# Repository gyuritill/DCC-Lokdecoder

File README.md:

# DCC-Lokdecoder
## Description
DCC multifunction decoder for H0 locomotives
## Features
- 1 motor H-bridge output
  - 3.6 A peak current
  - PWM frequency configurable (1-40 kHz)
  - overcurrent and temperature protected
- 10 function outputs
  - 115 mA per output
  - F0f, F0r, AUX1 and AUX2 are dimmable *todo*
  - mappable to F0-F12 function keys
- DCC asymmetry can be detected (for automatic brake control) *todo*
## Hardware
- 4-layer PCB esigned in KiCAD
- fairly standard components (available from Digi-Key, Farnell, Mouser, etc...)
- hand solderable (I did it too)
- 4 debug LEDs (red, yellow, green and blue)

|  |  |
| :---: | :---: |
| top side | bottom side |

## Firmware
- Arduino compatible programming (behaves like an UNO)
- DCC decoding by [NmraDcc](https://github.com/mrrwa/NmraDcc) library

## JMRI integration

|  |  |  |  |  |  |
| :---: | :---: | :---: | :---: | :---: | :---: |
| Basic  | Motor | Basic speed control | Speed table | Function map | Advanced |

## Install guide

1. Get the PCB (e.g. [JLCPCB](https://jlcpcb.com/)) and the components (e.g. [mouser](https://www.mouser.at/), [digikey](https://www.digikey.at/))
2. Solder the components. The SOIC with exposed pad is a bit tricky, it can be soldered from the other side with a big tip and a lot of flux.
3. Install the Arduino bootloader using the pads 5V, GND, SCK, MISO, MOSI, RST and an Arduino. [Arduino as ISP](https://www.arduino.cc/en/Tutorial/BuiltInExamples/ArduinoISP)
4. Uncomment the line `#define RESET_FACTORY_DEFAULTS` to fill the EEPROM with the default CV values
5. Upload the code using the pads 5V, GND, RX, TX, DTR and a USB TTL UART cable [like this](https://www.mouser.at/ProductDetail/FTDI/TTL-232R-5V-WE/?qs=OMDV80DKjRpCUAS6UR9QpQ%3D%3D)
6. Re-comment the line `#define RESET_FACTORY_DEFAULTS` to avoid resetting to factory defaults every time.
7. Upload the code again.
8. Add the decoder XML file to JMRI. In DecoderPro select "File-> Import Decoder File..." and browse to the decoder [XML](JMRI_decoder_file/Public_Domain_GTI_green.xml). It will take some time, then adds the decoder definition to the database.
9. Connect the T1 and T2 pads to the programming track of your DCC system.
10. Add new locomotive with the "New Loco" button and then "Read type from decoder". It should detect the correct type:

11. If everything is fine, you can install the decoder into your locomotive!
### Pinout
| Pad | Function |
| :-- | :-- |
| M1 | Motor 1 |
| M2 | Motor 2 |
| T1 | Track 1 |
| T2 | Track 2 |
| V+ | Positive common for function outputs (keep-alive capacitor positive) |
| F0f | F0 function output forward (open drain) |
| F0r | F0 function output reverse (open drain) |
| 1-8 | AUX function output n (open drain) |
| 5V | internal microcontroller +5V supply |
| GND | ground (keep alive capacitor negative) |
| SCK | ISP programming clock (connect to ISP SCK) |
| MISO | ISP programming read (connect to ISP MISO) |
| MOSI | ISP programming write (connect to ISP MOSI) |
| RST | ISP programming reset (connect to ISP reset output)
| RX | serial programming receive (connect to TTL UART TX) |
| TX | serial programming transmit (connect to TTL UART RX) |
| DTR | serial programming reset through a 100 nF capacitor (connect to TTL UART DTR) |

## Todo list
- [ ] CV15, CV16 decoder locking
- [ ] CV65 kick start
- [ ] CV67-94 speed table
- [ ] CV27 automatic brake control
- [ ] function output dimming
- [ ] motor fault check

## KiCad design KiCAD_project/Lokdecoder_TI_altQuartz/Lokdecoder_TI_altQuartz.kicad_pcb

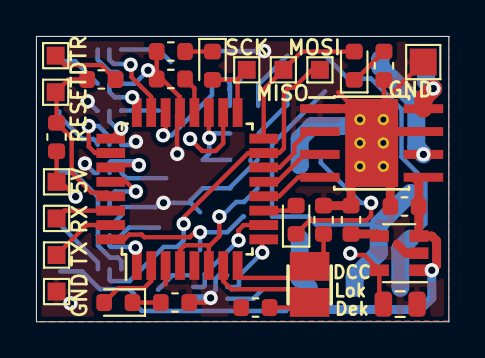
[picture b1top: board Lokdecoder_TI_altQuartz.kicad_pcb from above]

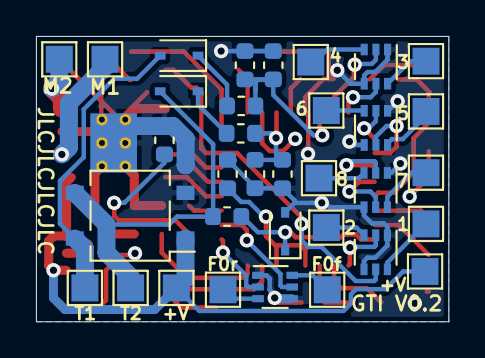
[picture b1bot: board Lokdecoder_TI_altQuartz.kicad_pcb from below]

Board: 4 copper layers, 22.9 x 15.8 mm, 63 parts (34 on the bottom side), 51 nets.

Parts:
C1, C2, C5, C10: 100nF; C_0603_1608Metric
C3: 470pF; C_0603_1608Metric
C4: 2.2uF; C_0805_2012Metric
C6, C7: 4.7uF; C_0603_1608Metric
C8, C9: 10pF; C_0603_1608Metric
D1: D_Bridge_+-AA; TO-269AA
D2: MM3Z4V7ST1G; D_SOD-323
D3, D4: NSR0530HT1G; D_SOD-323
D5: Ye_LED; LED_0603_1608Metric
D6: Gr_LED; LED_0603_1608Metric
D7: Rd_LED; LED_0603_1608Metric
D8: Bl_LED; LED_0603_1608Metric
IC1: MIC5205-5.0YM5-TR; SOT-23-5
IC2: ATMEGA328P-AUR; TQFP-32_7x7mm_P0.8mm
IC3: DRV8872DDAR; Texas_HTSOP-8-1EP_3.9x4.9mm_P1.27mm_EP2.95x4.9mm_Mask2.4x3.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
R1, R5, R6: 4.7k; R_0603_1608Metric
R2, R3, R4: 27k; R_0603_1608Metric
R7, R9, R10, R11: 1k; R_0603_1608Metric
T1, T2, T3, T4, T5: 2N7002DWCT; SOT-363_SC-70-6
TP1: M1; TestPoint_Pad_1.5x1.5mm
TP2: M2; TestPoint_Pad_1.5x1.5mm
TP3: T1; TestPoint_Pad_1.5x1.5mm
TP4: T2; TestPoint_Pad_1.5x1.5mm
TP5: GND; TestPoint_Pad_1.5x1.5mm
TP6, TP17: +V; TestPoint_Pad_1.5x1.5mm
TP7: F0f; TestPoint_Pad_1.5x1.5mm
TP8: F0r; TestPoint_Pad_1.5x1.5mm
TP9: 1; TestPoint_Pad_1.5x1.5mm
TP10: 2; TestPoint_Pad_1.5x1.5mm
TP11: 3; TestPoint_Pad_1.5x1.5mm
TP12: 4; TestPoint_Pad_1.5x1.5mm
TP13: 5; TestPoint_Pad_1.5x1.5mm
TP14: 6; TestPoint_Pad_1.5x1.5mm
TP15: 7; TestPoint_Pad_1.5x1.5mm
TP16: 8; TestPoint_Pad_1.5x1.5mm
TP18: RESET; TestPoint_Pad_1.0x1.0mm
TP19: SCK; TestPoint_Pad_1.0x1.0mm
TP20: MISO; TestPoint_Pad_1.0x1.0mm
TP21: MOSI; TestPoint_Pad_1.0x1.0mm
TP22: 5V; TestPoint_Pad_1.0x1.0mm
TP23: RX; TestPoint_Pad_1.0x1.0mm
TP24: TX; TestPoint_Pad_1.0x1.0mm
TP25: DTR; TestPoint_Pad_1.0x1.0mm
TP26: GND; TestPoint_Pad_1.0x1.0mm
X1: 16M; Crystal_SMD_2520-2Pin_2.5x2.0mm_HandSoldering

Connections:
+5V: C4.1, C5.2, IC1.5, IC2.4, IC2.6, IC2.18, R1.2, TP22.1
/A0: IC2.23, T4.2
/A1: IC2.24, T4.5
/A2: IC2.25, T5.2
/A3: IC2.26, T5.5
/A4: IC2.27, T3.2
/A5: IC2.28, T3.5
/A6: C6.2, IC2.19, R3.1, R5.1
/A7: C7.2, IC2.22, R4.1, R6.1
/AUX1: T2.6, TP9.1
/AUX1_TTL: IC2.1, T2.2
/AUX2: T2.3, TP10.1
/AUX2_TTL: IC2.15, T2.5, TP21.1
/AUX3: T4.6, TP11.1
/AUX4: T4.3, TP12.1
/AUX5: T5.6, TP13.1
/AUX6: T5.3, TP14.1
/AUX7: T3.6, TP15.1
/AUX8: T3.3, TP16.1
/D0: IC2.30, TP23.1
/D1: IC2.31, TP24.1
/D2: D2.1, IC2.32, R2.1
/D4: D8.2, IC2.2
/D5: IC2.9, T1.2
/D6: IC2.10, T1.5
/D7: D7.2, IC2.11
/D8: IC2.12, IC3.4
/D9: IC2.13, IC3.3
/D10: IC2.14, IC3.2
/D12: D6.2, IC2.16, TP20.1
/D13: D5.2, IC2.17, TP19.1
/DCC1: D1.4, D4.2, TP3.1
/DCC2: D1.3, D3.2, R2.2, TP4.1
/DTR: C1.2, TP25.1
/F0f: T1.6, TP7.1
/F0r: T1.3, TP8.1
/MOT1: IC3.6, TP1.1
/MOT2: IC3.8, TP2.1
/RESET: C1.1, IC2.29, R1.1, TP18.1
GND: C2.2, C3.1, C4.2, C5.1, C6.1, C7.1, C8.1, C9.1, C10.1, D1.2, D2.2, IC1.2, IC2.3, IC2.5, IC2.21, IC3.1, IC3.7, IC3.9, R5.2, R6.2, R7.1, R9.1, R10.1, R11.1, T1.1, T1.4, T2.1, T2.4, T3.1, T3.4, T4.1, T4.4, T5.1, T5.4, TP5.1, TP26.1
unnamed: C2.1, IC2.20
unnamed: C3.2, IC1.4
unnamed: C8.2, IC2.7, X1.1
unnamed: C9.2, IC2.8, X1.2
unnamed: D3.1, R3.2
unnamed: D4.1, R4.2
unnamed: D5.1, R9.2
unnamed: D6.1, R10.2
unnamed: D7.1, R11.2
unnamed: D8.1, R7.2
VCC: C10.2, D1.1, IC1.1, IC1.3, IC3.5, TP6.1, TP17.1

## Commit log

2021-02-12 Initial commit
    Initial commit
2021-02-14 Trim added,
    Arduino code:
    Comments extended, code cleanup
    - CV15/CV16 locking: local variables (unlockNumber, lockingNumber) created
    - CV27 autstop: : local variable (autoStop) created
    - CV65 kick-off: local variable (kickStart) created
    - CV66/CV95 speed trimming: feature implemented
2021-02-14 PCB images added
2021-02-14 JMRI pics
2021-02-16 Update dcc_decoder_green.ino
    F_CPU used to calculate PWM
    notifyCVAck fixed
2021-02-17 Create LICENSE
